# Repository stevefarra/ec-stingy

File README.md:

# ec-stingy
The EC(stin)G(y) provides an end-to-end design and implementation of a cost-effective, compact electrocardiogram. It connects to a computer via USB, monitoring a patient's cardiac signal and heart rate over time.

This project can serve as a template for any device measuring the heart's electrical activity and can be easily adapted to the user's needs. By open-sourcing the design files and code, the project aims to make medical hardware and technology more accessible and reduce the barrier to entry for prototyping.

## Directory Overview
Each folder corresponds to a specific stage of development or a component of the final product.

[`algorithm/`](algorithm/) - A simulation suite for prototyping digital signal filtering and peak detection.

[`firmware/`](firmware/) - Contains the program loaded into the MCU on-board the PCB.

[`spice/`](spice/) - Another simulation suite for prototyping the ECG analog front-end circuitry.

[`pcb/`](pcb/) - Schematic, footprint, and manufacturing files for the printed circuit board.

[`gui/`](gui/) - A desktop program to view the cardiac signal and heart rate readings over time.

[`docs/`](docs/) - Datasheets, README graphics, cited research papers, and other miscellanea.

## License

ec-stingy is licensed under the [MIT License](LICENSE). Unless otherwise stated, the repository owner authors all content, including source code, schematics, documentation, plots, animations, etc.

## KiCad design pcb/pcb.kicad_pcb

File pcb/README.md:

# PCB Design

## Directory overview
This directory includes several files with project metadata, but the key files are:

[`pcb.kicad_pro`](pcb.kicad_pro): KiCad 6 project file. Use this to properly load and open the schematic and layout files.

[`pcb.kicad_sch`](pcb.kicad_sch): The schematic file.

[`pcb.kicad_pcb`](pcb.kicad_pcb): The layout file.

[`libraries/`](libraries/): Contains symbols, footprints, and 3D models for components used in the project that are included in the KiCad library.

[`manufacturing/`](manufacturing/): Contains a bill of materials, a component placement file, and gerber files required to get the board produced.

## V for Via: Establishing a workflow
We heavily based the overall design and microcontroller layout on the [KiCad 6 STM32 tutorial](https://www.youtube.com/watch?v=aVUqaB0IMh4&pp=ygUNc3RtMzIga2ljYWQgNg%3D%3D), with several notable additions:

- The AD8232 and all of its associated circuitry (a near replica of the SPICE model in this project)
- The CP2102N USB-to-UART bridge controller, which acts as both a voltage regulator and PC interface in this design

We also added several peripherals to facilitate use and debugging:

- A micro-USB port, to power the board
- A 3.5 mm jack, to plug the electrode cable into
- A boot switch, to reset the microcontroller
- A serial wire debug pin header, to modify the firmware
- An ECG signal pin header, to inspect the analog signal
- LEDs to indicate a power connection and heartbeat readings, respectively

The schematic ends up falling roughly into 5 sections:

Before approaching the layout, we first consult PCB layout guidelines provided by the various ICs used. From the AD8232 datasheet:

> Keep all of the connections between high impedance nodes as short as  possible to avoid introducing additional noise and errors from  corrupting the signal. To maintain high CMRR over frequency, keep the input traces  symmetrical and length matched. Place safety and input bias  resistors in the same position relative to each input. In addition,  the use of a ground plane significantly improves the noise rejection of the system.

And from the STM32 datasheet:

> Each power-supply pair (VDD/VSS, VDDA/VSSA etc..) must be decoupled with filtering  ceramic capacitors as shown above. These capacitors must be placed as close as possible to or below the appropriate pins on the underside of the PCB, to ensure the good functionality of the device. The 10 nF capacitor must be ceramic (good quality) and it must be placed as close as possible to the chip.

With these principles in mind, a heavy draw of inspiration from the layout of the [SparkFun AD8232 breakout](https://www.sparkfun.com/products/12650), and a modest amount of trial-and-error, the resultant two-layer board layout came out like so:

## How cost-effective is it, really?
Time and effort were put into ensuring that the components chosen were economical and readily available to reduce the manufacturing cost as much as possible. Below is a breakdown of the per-board manufacturing costs at the time of writing this, ordering from JLCPCB (minimum quantity of 5):

<div align="center">

| Category   | Cost (CAD)  |
|------------|-------------|
| Passives   | $0.50       |
| Connectors | $1.13       |
| ICs        | $6.86       |
| Assembly   | $3.07       |

</div>

Although it's difficult to directly compare this device to commercially-available products, the closest would be a Holter monitor like the [Prince 180B1 from Heal Force](http://www.healforce.com/en/html/products/portableecgmonitors/605.html) which currently retails at \$140 CAD. The total cost of our board comes to $11.56 CAD, which is roughly 9% of the market equivalent. Not bad!

## The cutting room floor
**Commission a board review:** Despite passing KiCad's electrical and design rule checks, a third-party formal review could validate the schematic and layout. This review would also ensure adherence to best practices on differential trace length matching, passive component sizing, and decoupling capacitor layout, helping to prevent potential costly or time-consuming errors before manufacturing.

**Add more safeguards:** This device is far from being fully IEC 60601-compliant, but replacing the PC power supply with an external battery, adding TVS diodes to sensitive traces for ESD protection, and using an optocoupler to provide electrical isolation between the patient and the ECG would all increase the device's overall safety.

**Compactify the layout:** The board size comes in at roughly 61 mm by 33 mm, but there is still quite a bit of unused space which could be used for more peripherals or done away with altogether by rearranging components.

**Design an enclosure:** A hard casing with cutouts for peripheral access and LED viewing could enhance this project. The board already has mounting holes for fastening. KiCad's [StepUp](https://www.kicad.org/external-tools/stepup/) tool allows the 3D model above to be easily imported into FreeCAD and would come in handy here.

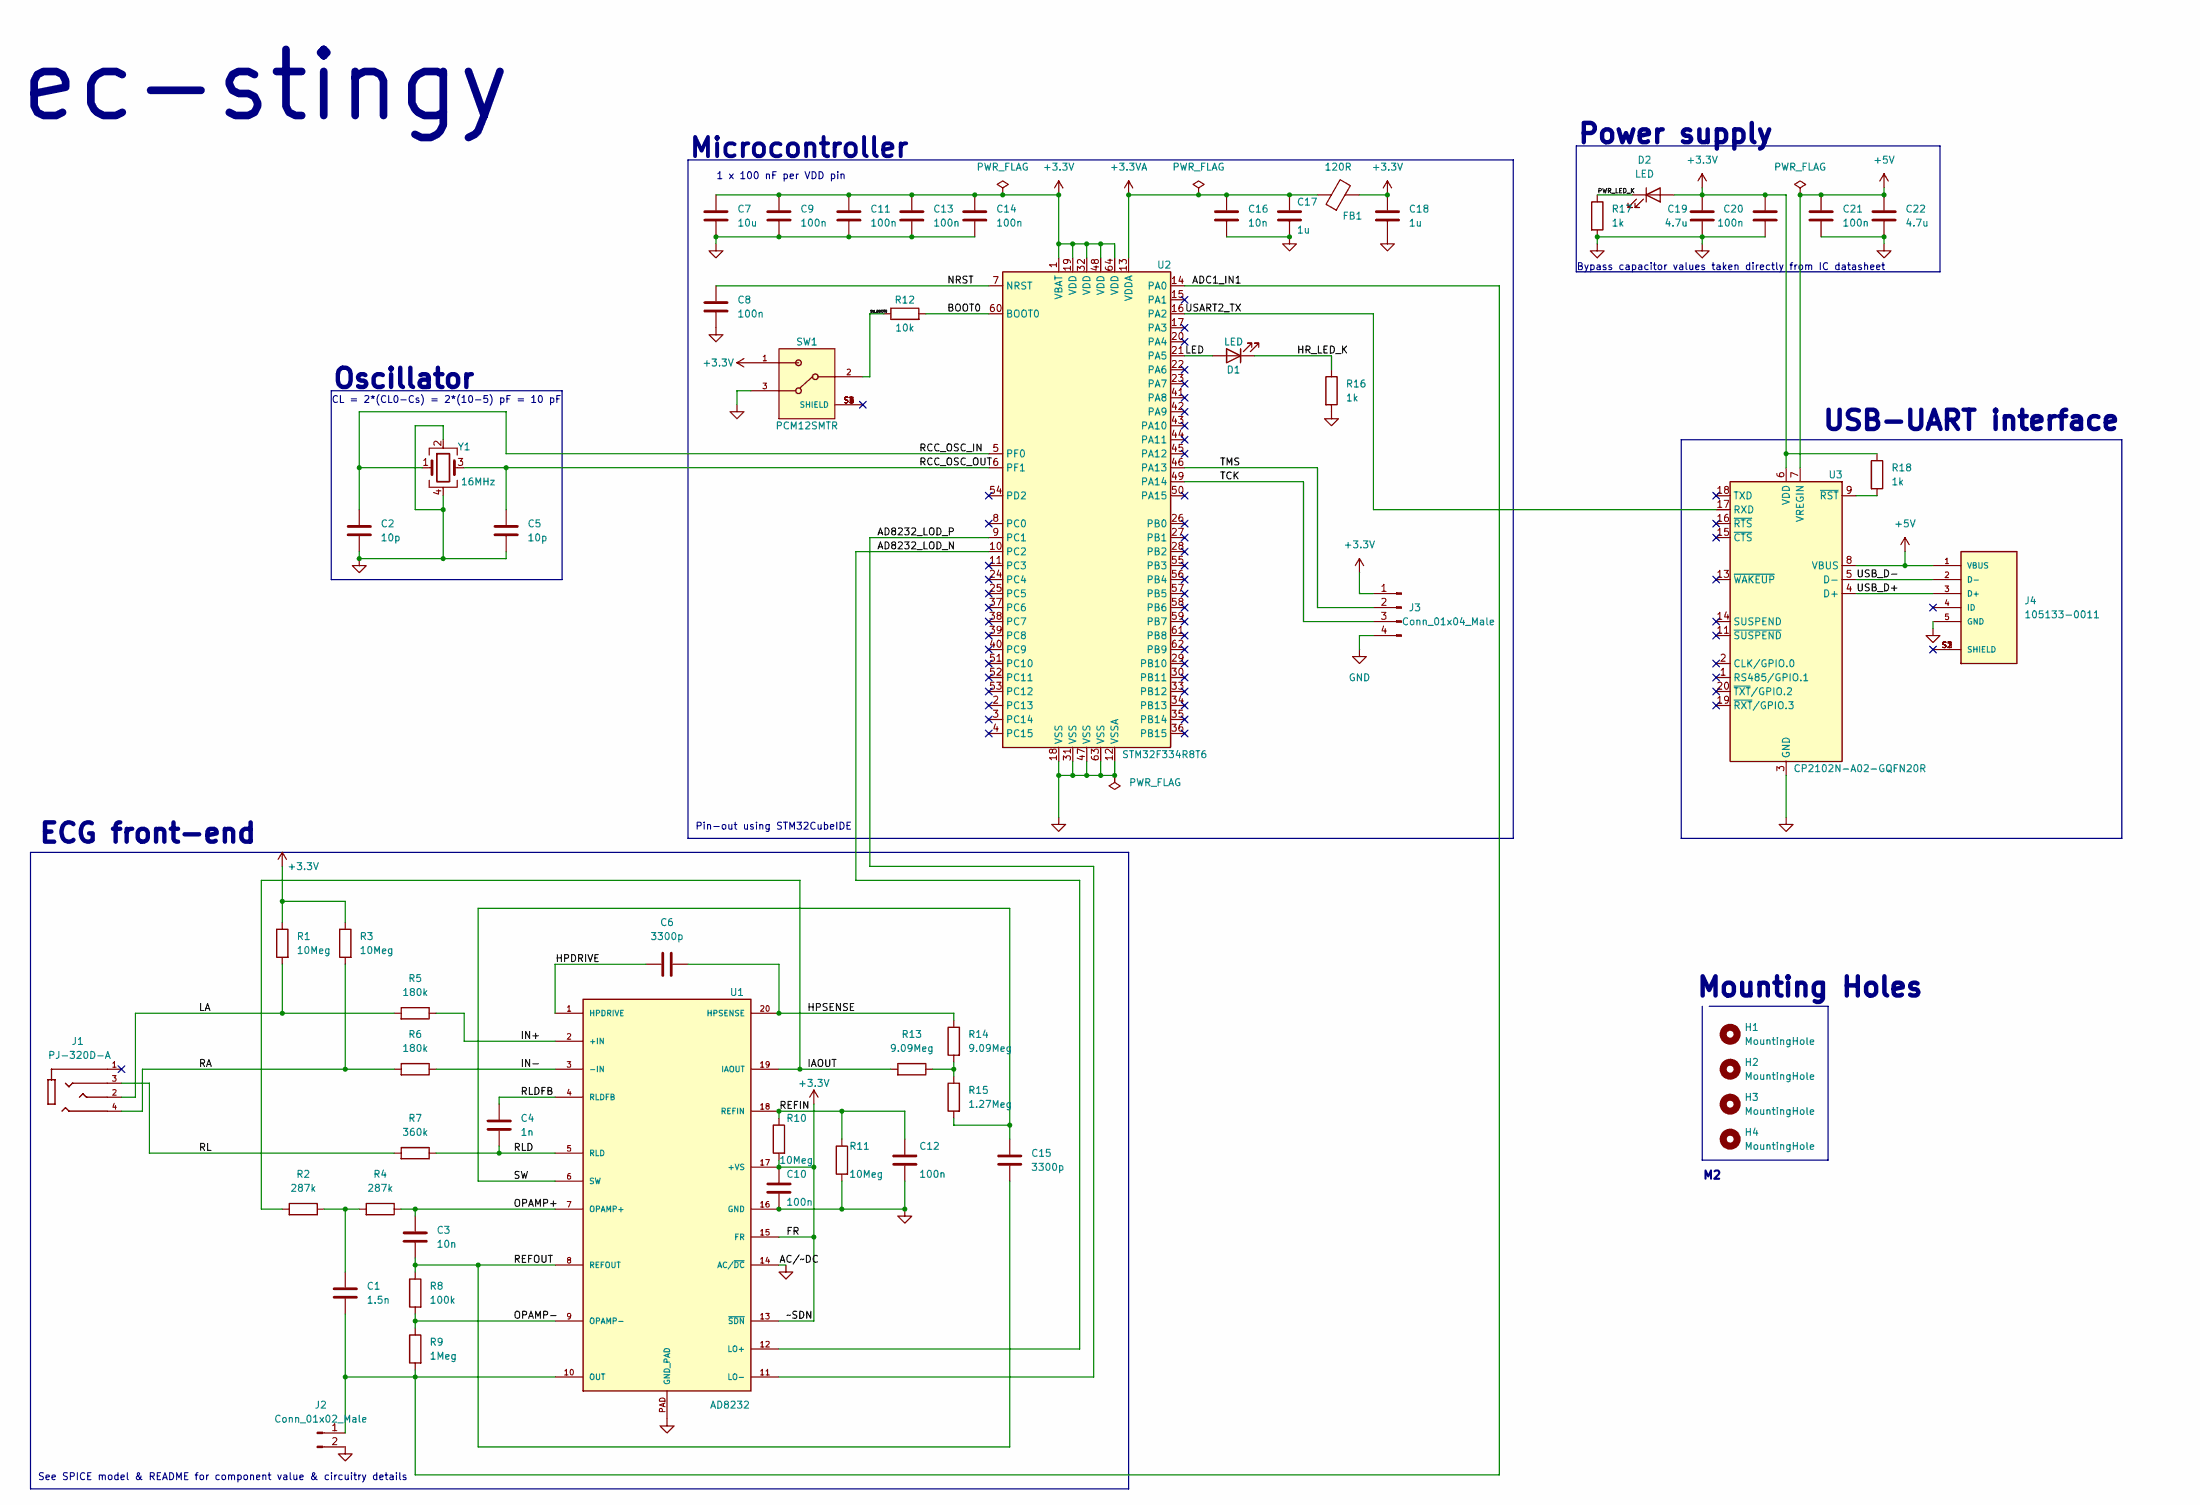
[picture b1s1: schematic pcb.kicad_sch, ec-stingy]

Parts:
C1: 1.5n; C_0402_1005Metric
C2, C5: 10p; C_0402_1005Metric
C3, C16: 10n; C_0402_1005Metric
C4: 1n; C_0402_1005Metric
C6, C15: 3300p; C_0402_1005Metric
C7: 10u; C_0603_1608Metric
C8, C9, C10, C11, C12, C13, C14, C20, C21: 100n; C_0402_1005Metric
C17, C18: 1u; C_0603_1608Metric
C19, C22: 4.7u; C_0603_1608Metric
D1, D2: LED; LED_0603_1608Metric
FB1: 120R; L_0603_1608Metric
H1, H2, H3, H4: MountingHole; MountingHole_2.2mm_M2
J1: PJ-320D-A; HRO_PJ-320D-A; PARTREV B
J2: Conn_01x02_Male; PinHeader_1x02_P2.54mm_Vertical
J3: Conn_01x04_Male; PinHeader_1x04_P2.54mm_Vertical
J4: 105133-0011; MOLEX_105133-0011; PARTREV C
R1, R3, R10, R11: 10Meg; R_0603_1608Metric
R2, R4: 287k; R_0603_1608Metric
R5, R6: 180k; R_0402_1005Metric
R7: 360k; R_0603_1608Metric
R8: 100k; R_0402_1005Metric
R9: 1Meg; R_0603_1608Metric
R12: 10k; R_0402_1005Metric
R13, R14: 9.09Meg; R_0603_1608Metric
R15: 1.27Meg; R_0603_1608Metric
R16, R17, R18: 1k; R_0402_1005Metric
SW1: PCM12SMTR; SW_PCM12SMTR
U1: AD8232; LFCSP_20
U2: STM32F334R8T6; LQFP-64_10x10mm_P0.5mm
U3: CP2102N-A02-GQFN20R; SILABS_CP2102N-A02-GQFN20R
Y1: 16MHz; Crystal_SMD_3225-4Pin_3.2x2.5mm

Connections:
+3.3V: C7.1, C9.1, C10.1, C11.1, C13.1, C14.1, C18.1, C19.1, C20.1, D2.2 (A), FB1.2, J3.1, R1.1, R3.1, R10.2, R18.1, SW1.1, U1.13 (~SDN), U1.15 (FR), U1.17 (+VS), U2.1 (VBAT), U2.19 (VDD), U2.32 (VDD), U2.48 (VDD), U2.64 (VDD), U3.6 (VDD)
+3.3VA: C16.1, C17.1, FB1.1, U2.13 (VDDA)
+5V: C21.1, C22.1, J4.1 (VBUS), U3.7 (VREGIN), U3.8 (VBUS)
/AD8232_LOD_N: U1.12 (LO+), U2.10 (PC2)
/AD8232_LOD_P: U1.11 (LO-), U2.9 (PC1)
/ADC1_IN1: C1.2, J2.1, R9.2, U1.10 (OUT), U2.14 (PA0)
/BOOT0: R12.2, U2.60 (BOOT0)
/HPDRIVE: C6.1, U1.1 (HPDRIVE)
/HPSENSE: C6.2, R14.1, U1.20 (HPSENSE)
/HR_LED_K: D1.1 (K), R16.1
/IAOUT: R2.2, R13.2, U1.19 (IAOUT)
/IN+: R5.1, U1.2 (+IN)
/IN-: R6.1, U1.3 (-IN)
/LA: J1.2, R1.2, R5.2
/LED: D1.2 (A), U2.21 (PA5)
/NRST: C8.1, U2.7 (NRST)
/OPAMP+: C3.1, R4.1, U1.7 (OPAMP+)
/OPAMP-: R8.2, R9.1, U1.9 (OPAMP-)
/PWR_LED_K: D2.1 (K), R17.1
/RA: J1.4, R3.2, R6.2
/RCC_OSC_IN: C2.1, U2.5 (PF0), Y1.1
/RCC_OSC_OUT: C5.1, U2.6 (PF1), Y1.3
/REFIN: C12.2, R10.1, R11.1, U1.18 (REFIN)
/REFOUT: C3.2, C15.1, R8.1, U1.8 (REFOUT)
/RL: J1.3, R7.2
/RLD: C4.2, R7.1, U1.5 (RLD)
/RLDFB: C4.1, U1.4 (RLDFB)
/SW: C15.2, R15.2, U1.6 (SW)
/SW_BOOT0: R12.1, SW1.2
/TCK: J3.3, U2.49 (PA14)
/TMS: J3.2, U2.46 (PA13)
/USART2_TX: U2.16 (PA2), U3.17 (RXD)
/USB_D+: J4.3 (D+), U3.4 (D+)
/USB_D-: J4.2 (D-), U3.5 (D-)
GND: C2.2, C5.2, C7.2, C8.2, C9.2, C10.2, C11.2, C12.1, C13.2, C14.2, C16.2, C17.2, C18.2, C19.2, C20.2, C21.2, C22.2, J2.2, J3.4, J4.5 (GND), R11.2, R16.2, R17.2, SW1.3, U1.14 (AC/~DC), U1.16 (GND), U1.PAD (GND_PAD), U2.12 (VSSA), U2.18 (VSS), U2.31 (VSS), U2.47 (VSS), U2.63 (VSS), U3.3 (GND), U3.12 (GND), U3.21 (GND), Y1.2, Y1.4
unnamed: C1.1, R2.1, R4.2
unnamed: R13.1, R14.2, R15.1
unnamed: R18.2, U3.9 (~RST)

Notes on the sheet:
Mounting Holes
Bypass capacitor values taken directly from IC datasheet
CL = 2*(CL0-Cs) = 2*(10-5) pF = 10 pF
1 x 100 nF per VDD pin
Microcontroller
Pin-out using STM32CubeIDE
ECG front-end
Power supply
USB-UART interface
Oscillator
ec-stingy
See SPICE model & README for component value & circuitry details

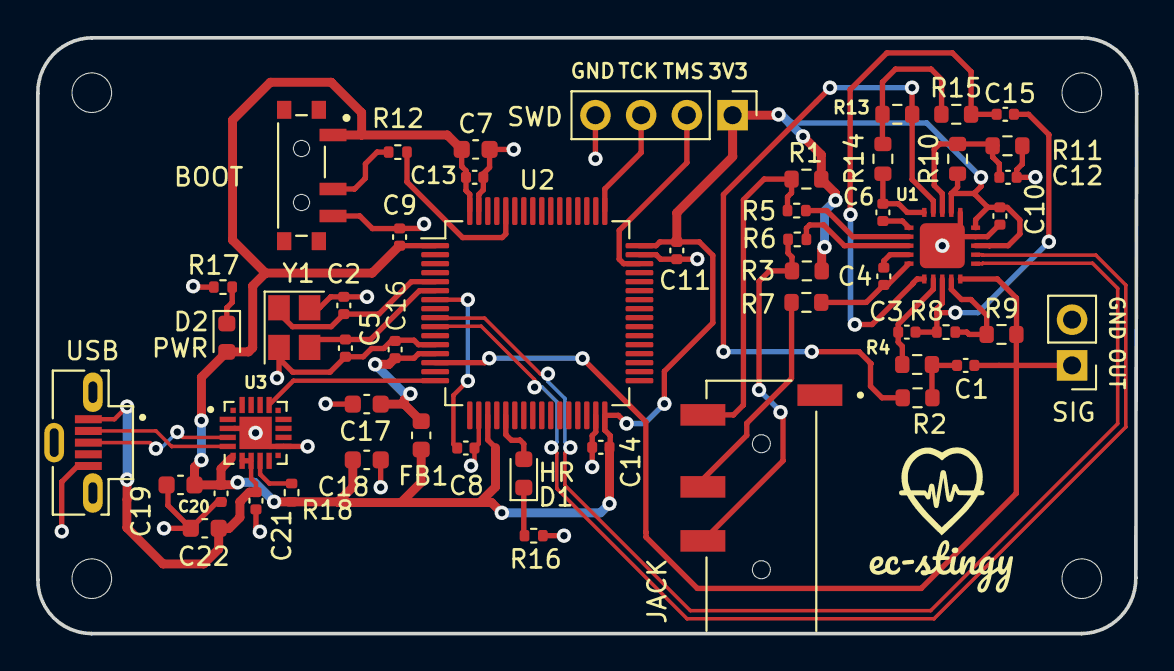
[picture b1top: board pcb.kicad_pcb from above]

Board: 2 copper layers, 61.0 x 33.1 mm, 56 parts (0 on the bottom side), 38 nets.

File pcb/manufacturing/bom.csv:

"Source:","D:\Repositories\ec-stingy\pcb\pcb.kicad_sch"
"Date:","2023-07-19 12:03:35 PM"
"Tool:","Eeschema (6.0.9)"
"Generator:","D:\Program Files\KiCad\6.0\bin\scripting\plugins/bom_csv_grouped_by_value_with_fp.py"
"Component Count:","56"
"Ref","Qnty","Value","Cmp name","Footprint","Description","Vendor"
"C1, ","1","1.5n","C","Capacitor_SMD:C_0402_1005Metric","Unpolarized capacitor",""
"C2, C5, ","2","10p","C","Capacitor_SMD:C_0402_1005Metric","Unpolarized capacitor",""
"C3, C16, ","2","10n","C","Capacitor_SMD:C_0402_1005Metric","Unpolarized capacitor",""
"C4, ","1","1n","C","Capacitor_SMD:C_0402_1005Metric","Unpolarized capacitor",""
"C6, C15, ","2","3300p","C","Capacitor_SMD:C_0402_1005Metric","Unpolarized capacitor",""
"C7, ","1","10u","C","Capacitor_SMD:C_0603_1608Metric","Unpolarized capacitor",""
"C8, C9, C10, C11, C12, C13, C14, C20, C21, ","9","100n","C","Capacitor_SMD:C_0402_1005Metric","Unpolarized capacitor",""
"C17, C18, ","2","1u","C","Capacitor_SMD:C_0603_1608Metric","Unpolarized capacitor",""
"C19, C22, ","2","4.7u","C","Capacitor_SMD:C_0603_1608Metric","Unpolarized capacitor",""
"D1, D2, ","2","LED","LED","LED_SMD:LED_0603_1608Metric","Light emitting diode",""
"FB1, ","1","120R","FerriteBead","Inductor_SMD:L_0603_1608Metric","Ferrite bead",""
"J1, ","1","PJ-320D-A","PJ-320D-A","PJ-320D-A:HRO_PJ-320D-A","",""
"J2, ","1","Conn_01x02_Male","Conn_01x02_Male","Connector_PinHeader_2.54mm:PinHeader_1x02_P2.54mm_Vertical","Generic connector, single row, 01x02, script generated (kicad-library-utils/schlib/autogen/connector/)",""
"J3, ","1","Conn_01x04_Male","Conn_01x04_Male","Connector_PinHeader_2.54mm:PinHeader_1x04_P2.54mm_Vertical","Generic connector, single row, 01x04, script generated (kicad-library-utils/schlib/autogen/connector/)",""
"J4, ","1","105133-0011","105133-0011","105133-0011:MOLEX_105133-0011","",""
"R1, R3, R10, R11, ","4","10Meg","R","Resistor_SMD:R_0603_1608Metric","Resistor",""
"R2, R4, ","2","287k","R","Resistor_SMD:R_0603_1608Metric","Resistor",""
"R5, R6, ","2","180k","R","Resistor_SMD:R_0402_1005Metric","Resistor",""
"R7, ","1","360k","R","Resistor_SMD:R_0603_1608Metric","Resistor",""
"R8, ","1","100k","R","Resistor_SMD:R_0402_1005Metric","Resistor",""
"R9, ","1","1Meg","R","Resistor_SMD:R_0603_1608Metric","Resistor",""
"R12, ","1","10k","R","Resistor_SMD:R_0402_1005Metric","Resistor",""
"R13, R14, ","2","9.09Meg","R","Resistor_SMD:R_0603_1608Metric","Resistor",""
"R15, ","1","1.27Meg","R","Resistor_SMD:R_0603_1608Metric","Resistor",""
"R16, R17, R18, ","3","1k","R","Resistor_SMD:R_0402_1005Metric","Resistor",""
"SW1, ","1","PCM12SMTR","PCM12SMTR","PCM12SMTR:SW_PCM12SMTR","",""
"U1, ","1","AD8232","AD8232","AD8232:LFCSP_20","",""
"U2, ","1","STM32F334R8T6","STM32F334R8Tx","Package_QFP:LQFP-64_10x10mm_P0.5mm","ARM Cortex-M4 MCU, 64KB flash, 12KB RAM, 72MHz, 2-3.6V, 51 GPIO, LQFP-64",""
"U3, ","1","CP2102N-A02-GQFN20R","CP2102N-Axx-xQFN20","CP2102N-A02-GQFN20R:SILABS_CP2102N-A02-GQFN20R","USB to UART master bridge, QFN-20",""
"Y1, ","1","16MHz","Crystal_GND24","Crystal:Crystal_SMD_3225-4Pin_3.2x2.5mm","Four pin crystal, GND on pins 2 and 4",""

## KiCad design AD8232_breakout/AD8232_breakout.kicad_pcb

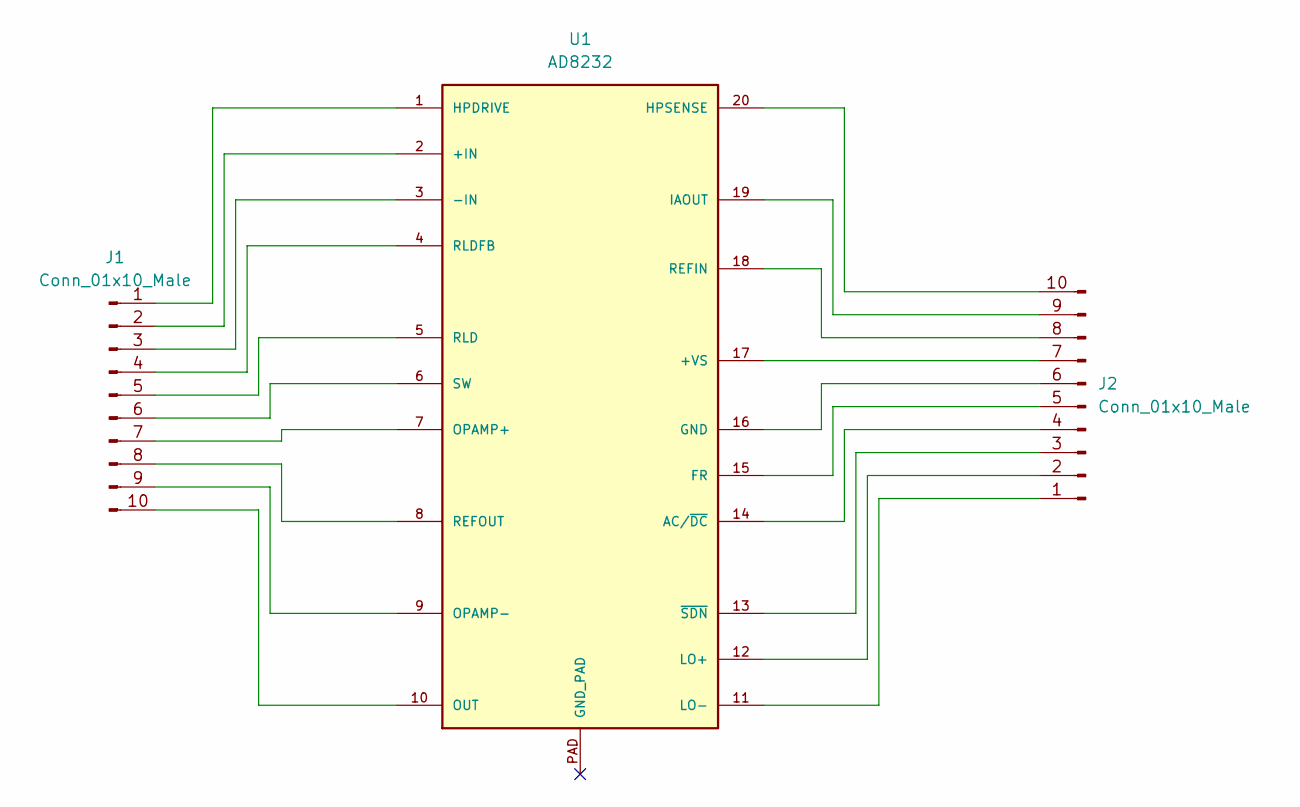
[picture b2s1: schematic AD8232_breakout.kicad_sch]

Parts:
J1, J2: Conn_01x10_Male; PinHeader_1x10_P2.54mm_Vertical
U1: AD8232; LFCSP_20

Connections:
unnamed: J1.1, U1.1 (HPDRIVE)
unnamed: J1.2, U1.2 (+IN)
unnamed: J1.3, U1.3 (-IN)
unnamed: J1.4, U1.4 (RLDFB)
unnamed: J1.5, U1.5 (RLD)
unnamed: J1.6, U1.6 (SW)
unnamed: J1.7, U1.7 (OPAMP+)
unnamed: J1.8, U1.8 (REFOUT)
unnamed: J1.9, U1.9 (OPAMP-)
unnamed: J1.10, U1.10 (OUT)
unnamed: J2.1, U1.11 (LO-)
unnamed: J2.2, U1.12 (LO+)
unnamed: J2.3, U1.13 (~SDN)
unnamed: J2.4, U1.14 (AC/~DC)
unnamed: J2.5, U1.15 (FR)
unnamed: J2.6, U1.16 (GND)
unnamed: J2.7, U1.17 (+VS)
unnamed: J2.8, U1.18 (REFIN)
unnamed: J2.9, U1.19 (IAOUT)
unnamed: J2.10, U1.20 (HPSENSE)

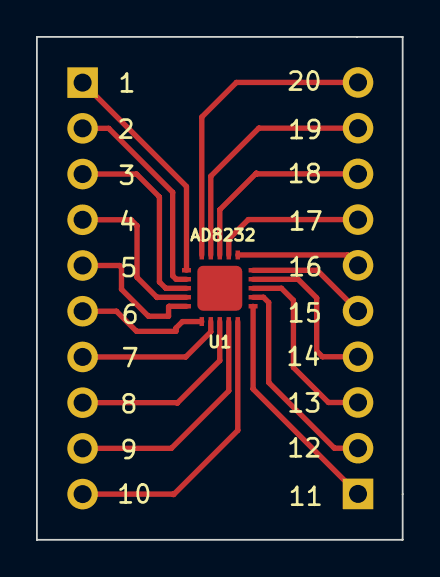
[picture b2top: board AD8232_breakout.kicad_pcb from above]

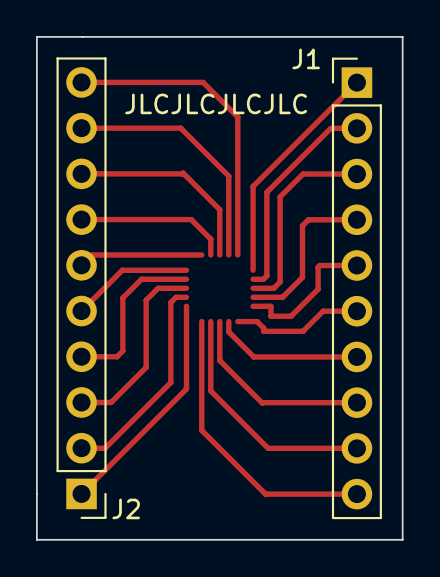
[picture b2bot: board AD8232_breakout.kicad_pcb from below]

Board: 2 copper layers, 20.3 x 27.9 mm, 3 parts (2 on the bottom side), 20 nets.

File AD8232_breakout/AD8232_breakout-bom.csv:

Comment,Designator,Footprint,JLCPCB Part #(optional)
Conn_01x10_Male,"J1, J2",Connector_PinHeader_2.54mm:PinHeader_1x10_P2.54mm_Vertical,
AD8232,U1,AD8232:LFCSP_20,C43216

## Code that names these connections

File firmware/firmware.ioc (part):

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Mcu.Name=STM32F334R(6-8)Tx
Mcu.Package=LQFP64
Mcu.UserName=STM32F334R8Tx
PA0.Mode=IN1-Single-Ended
PA0.Signal=ADC1_IN1
PA13.GPIOParameters=GPIO_Label
PA13.GPIO_Label=TMS
PA13.Mode=Serial_Wire
PA13.Signal=SYS_JTMS-SWDIO
PA14.GPIOParameters=GPIO_Label
PA14.GPIO_Label=TCK
PA14.Mode=Serial_Wire
PA14.Signal=SYS_JTCK-SWCLK
PA2.Mode=Asynchronous
PA2.Signal=USART2_TX
PA3.Mode=Asynchronous
PA3.Signal=USART2_RX
PA5.GPIOParameters=GPIO_Label
PA5.GPIO_Label=LED
PA5.Signal=GPIO_Output
PB3.GPIOParameters=GPIO_Label
PB3.GPIO_Label=SWO
PB3.Signal=SYS_JTDO-TRACESWO
PC0.GPIOParameters=GPIO_Label
PC0.GPIO_Label=AD8232_LOD_P
PC0.Signal=GPIO_Input
PC1.GPIOParameters=GPIO_Label
PC1.GPIO_Label=AD8232_LOD_N
PC1.Signal=GPIO_Input
PC14\ /\ OSC32_IN.Signal=RCC_OSC32_IN
PC15\ /\ OSC32_OUT.GPIOParameters=GPIO_Label
PC15\ /\ OSC32_OUT.GPIO_Label=RCC_OSC32_OUT
PC15\ /\ OSC32_OUT.Signal=RCC_OSC32_OUT
PF0\ /\ OSC_IN.Mode=HSE-External-Oscillator
PF0\ /\ OSC_IN.Signal=RCC_OSC_IN
PF1\ /\ OSC_OUT.Mode=HSE-External-Oscillator
PF1\ /\ OSC_OUT.Signal=RCC_OSC_OUT
RCC.HSEPLLFreq_Value=8000000
RCC.HSE_VALUE=8000000
RCC.SYSCLKFreq_VALUE=64000000
RCC.SYSCLKSourceVirtual=RCC_SYSCLKSOURCE_PLLCLK
board=NUCLEO-F334R8
boardIOC=true

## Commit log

2022-07-04 Create hello.txt
    Initial commit
2022-07-05 install wfdb package
2022-07-05 initial sims
2022-07-05 included spice sim
2022-07-05 include op amp in sim
2022-07-05 rm .gitignore files
2022-07-05 changed comments
2022-07-05 add plot code
2022-07-05 small changes
2022-07-05 AD8232 sim files
2022-07-06 sim working
2022-07-06 minor changes
2022-07-07 working circuit
2022-07-07 add PanTompkinsQRS module
2022-07-07 submodule update test
2022-07-07 Revert "submodule update test"
    This reverts commit c0c1ac6610184bc7bb7555ce234fa81dded9fc61.
2022-07-07 Revert "add PanTompkinsQRS module"
    This reverts commit b35968e5c2f37de6799932c3f8efdf9c61a29545.
2022-07-13 img rename
2022-09-29 add all changes
2022-10-11 i goofed something with the circuit lol
2022-11-09 ecg_sim updated with more documentation and simulation completes in reasonable time, still need to double check that everything is accounted for
2022-12-15 include bom
2022-12-15 add test file
2022-12-23 finished ad8232 breakout pcb
2022-12-23 test file for wsl
2023-01-09 added another application circuit spice file
2023-01-09 added missing capcaitor and fixed voltage sources
2023-02-16 added script to print serial port data to file
2023-02-16 modify gitignore
2023-02-16 .gitignore refresh
2023-02-16 reading ecg signal on mcu
2023-03-13 non-blocking ADC reads
2023-03-14 removed remnants of PanTompkins from main header and source files
2023-04-06 modularized code
2023-04-13 peak detection working but sample rate caps at ~140 Hz
2023-04-14 added C program to test signal processing
2023-05-09 progress
2023-05-09 first filter works in C
2023-05-09 waveforms look good
2023-05-11 more touches
2023-05-12 peak detection implemented but not working
2023-05-12 last commit before filter restructuring
2023-05-17 refactored
2023-05-17 added macros
2023-05-18 peak detection implemented but weird linter warning
2023-05-18 mostly accurate readings
2023-05-18 readings mostly accurate
2023-05-19 peak detection finds max in original signal. works in MATLAB, one beat wrong in C
2023-05-28 current state
2023-05-29 stack reallocation works but need to re-work C prototype program to use smaller buffers wherever possible
2023-05-30 highpass filter works
2023-06-01 algo signals looking good
2023-06-02 non-blocking works!
2023-06-02 good ADC readings
2023-06-03 bpm readings
2023-06-05 prints rounded val to uart
2023-06-05 changed if statement nesting, readings still good
2023-06-09 working state
2023-06-09 serial format adjustments
2023-06-09 qt boilerplate builds successfully
2023-06-11 gui plots look good
2023-06-11 added titles to plots
2023-06-14 gui good, notch filter working in C program but code could be made cleaner
2023-06-14 cleaned up Octave scripts
2023-06-14 added more comments
2023-06-15 put notch filter before low pass
2023-06-15 added notch filtering before low pass on STM32 but offset is weird
2023-06-15 fixed moving average bug
2023-06-15 fixed minor things after merging experiment into main
2023-06-16 added more comments and updated .gitignore
2023-06-16 remove cached files
2023-06-16 remove DS store
2023-06-16 remove extra gitignore
2023-06-16 more updates to .gitignore
2023-06-16 update .gitignore again
2023-06-16 removed ignored files from repo
2023-06-16 added comments to stm32 main()
2023-06-17 refactored octave script and added bode plot
2023-06-19 none of the cardiac monitor spice sims work, sticking to hr measured at hands
2023-06-19 file clean-up
2023-06-27 fixed grounding on spice model, progress on schematic
2023-06-29 added cardiac monitor config spice model
2023-06-29 reconstructed schematic
2023-06-30 schematic mostly done
2023-06-30 assigning footprints progress
2023-06-30 remove hr spice file
2023-07-05 progress on layout
2023-07-07 more pcb progress
2023-07-08 new visual
2023-07-08 high pass filter visual
2023-07-08 remove legend
2023-07-08 reduced graph size
2023-07-08 triangle filter added
2023-07-08 added threshold plot
2023-07-08 r peaks plot
2023-07-08 restored Octave algo script
2023-07-11 README progress
2023-07-11 added docs
2023-07-12 spice readme prog
2023-07-12 more prog
2023-07-12 more readme prog
2023-07-18 readme prog
2023-07-19 minor readme changes
2023-07-19 pcb finished
2023-07-24 refresh git index based on updated .gitignore
2023-07-25 refactor gui folder
2023-07-26 gui readme prog
2023-07-26 proofread readmes
2023-07-26 proofread high-level readme
2023-07-26 fix visual
2023-07-26 fix italics
2023-07-26 minor fix
2023-07-26 minor addition
2023-08-01 add paper
2023-08-08 more readme updates
2023-08-08 added references
